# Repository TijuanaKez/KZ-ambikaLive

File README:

Ambika Live! (we'll call it that for now)

This project is a series of modifications (improvements) over the top of the YAM fork of the original firmware for Ambika.

Changes:

ENV/LFO/MOD slot cycling with page buttons:

	- Repeatedly pressing buttons for ENV/LFO and MOD pages now cycles through slots.
	- Makes for muscle memory access to what you’re after quickly. e.g (double click for LFO2)
	- Good for 2 handed operation.

Turbo patch name editing!

	- Can now press A,a or 1 to jump to those characters, insert space, or move cursor with buttons.
	- Super quick 2 handed name editing!
	- ( A | a | 1 | _ | <- | -> save | exit)

'Drum' modulation destinations.

	- Same as Osc1 and Osc2 destinations, but with +/-32 semitones range for wider pitch envelopes.
	- The standard coarse pitch mod destinations don't have enough range for good drum sounds, and the envelopes curves arent steep enough.
	- But, the standard envelopes can be 'squared' by using the modifiers for a steeper curve. Routing one of these 'squared' envelopes to 'drum' destination with an amount of 32, Ambika can achieve much better drum sounds or 808 like sounds.
	- e.g Modul.  1|srce mod1|dest drm1|amnt   32
	-     Modif.  1|in1  env1|in2  env1|oper prod  (squaring the Env1 envelope)

Solo polyphony mode:

	-Same as mono but only uses a single voice. Great if you designed a patch for a single voice (legato/glide) but want to load it onto a part that has multiple voices assigned and don’t want the unison/stacked sound.

Arp Latch Mode:

	-Acts like the arp latch on Microkorg. Pressing a key once triggers note on, a second time for note off.

Chord Sequencer mode:

	-In Chord Seq mode, the sequencer will pass each block of 4 consecutive notes on to the arp as a chord.
	-The 'lenp' parameter defines how many steps between chord changes.
	-The note sequence length is locked to 16 steps (4 chords) for now.
	-Use rests to reduce the number of notes in each chord.

Sequencer Tweaks:

	-Rests are now displayed similar to a tracker where '---' is displayed when there is no note assigned.
	-Makes for more visual drum sequences.

Performance Page Tweaks

	-When in the main performance page, the first 4 buttons now act as part mutes. Cool for jamming with the chord sequencer!
	-Button 5 resyncs the clocks. This is a bit of a workaround for the moment until I can get them to stay locked without having to resync (any ideas?)

Optional CC Maps (pref page 2)

	-Can choose between Ambika standard, Shruthi XT, and Novation Launchkey CC assignments (more to come).
	-Ideally these would be loadable from SDcard, but the only way I can think to fit them would be to use the boot loader to overwrite CC maps in progmem which is beyond my skills :frowning:

Unfortunately these mods will not be fully compatible with saved patches, though updating them would not be hard. It would mainly be checking the polyphony mode is correct, and resaving.

Work in progress…

Launchkey integration!

USB host for Launchkey via Arduino micro+micro USB Host via port 7 for connecting Launchkey directly to the Ambika.
Buss power the Arduino micro+Launchkey (might need regulator upgrade on ambika???)
Launchkey Sequencer mode: RGB pads will show sequence ‘playhead’ with one color, and knobs will edit either note, seq1 or seq2 depending on mode. Idle pads will show other colors whose intensity will represent the current sequencer values.
(‘Launchkey Seq’ mode is already in prefs page 2, but only shows the playhead now)

Source Code: Macros for enabling/disabling various functions to free up space temporarily to mess around.

The YAM fork of the original firmware can be found here (https://github.com/bjoeri/ambika).
As this is forked on top of YAM, all the YAM changes also apply.

Notes on building the source:

	- For the voicecard build to succeed, avr-gcc 4.3.3 must be used. Any later versions will build, but result in a silent voice card.
	- For the controller, avr-gcc 4.3.3 build will break our file size limit (61440 bytes)
	- But 4.5.1 will successfully build the controller and save us about 2700 bytes!!!

--- YAM Notes ---

Y A M - Yet Another Mutation

This is a project for an alternative firmware for Ambika, a hybrid MIDI polysynth and voicecard host from Mutable Instruments. 

Here's a short summary of changes _compared_ to official Ambika firmware:

* PolyBlep implementations replace the original band-limited 'saw' and 'square' oscillators for higher fidelity and less memory footprint (Polyblep implementation inspired by, but less general than, Emilies prototype for STM). 

* 'square' is now a Polyblep oscillator with more proper sounding PWM, i.e. more edginess, and no loudness drop for PWM modulation parameter above 0. 

* 'saw' is now a Polyblep oscillator (without any high pass pre-filtering and the modulation is different). The parameter for saw now add mix of a 2nd saw edge, resulting in a saw with sub oscillator (actually super oscillator) sound. 

* 'triangle' is no longer band-limited (to reduce memory footprint) and is folded (instead of clipped) upon modulation. 

* Added a quad PWM oscillator ('qpwm') very similar to the quad saw ('pad'). The modulation parameter simultaneously affects both detuning of the four pwm oscillators and the pulse width.

* Added an alternative FM oscillator ('fmfb') with feedback modulation. Just as for the regular FM oscillator, the modulation parameter defines the FM amount, but for modulation values above 64 increasing amount of feedback is added. At moderate levels the feedback adds 'grit'. At higher settings it adds digital distortion (deliberately left in).

* Added a 'csaw' Polyblep oscillator rather similar to the CS-80 inspired saw oscillator for Braids. Without modulation it's a plain saw (identical to 'saw'). Modulation adds a 'notch' discontinuity before the ramp.

* Ported phase57 mods for velocity and keyboard tracking to filter page and CC & NRPN assignments (104 and 105 respectively). Also, the active editing parameter is displayed in all uppercase characters. (http://blog.phase57.com/index.php/ambika/code for more details.) 

NOTES ON PATCH (PROGRAM) COMPATIBILITY with official Ambika firmware: 
Due to qualitative differences of the 'saw' and 'square' oscillators etc, levels may have to be adjusted somewhat to mimic original patches. If you really miss the original saw oscillator from the official firmware, this one is still available as 'oldsaw' (it's high-pass sampled and have a different character). In order to maximize patch (actually program) backwards compatibility, the added oscillators are put at the end of the oscillator selection (even though this means fmfb is not next to fm etc).

This repository was originally a copy of the Mutable Instruments GitHub Ambika repository at https://github.com/pichenettes/ambika
 
Original developer: Emilie Gillet (olivier@mutable-instruments.net)

The firmware is released under a GPL3.0 license. It includes a variant of the formant synthesis algorithm used in Peter Knight's Cantarino speech synthesizer.

The PCB layouts and schematics, documentation, analyses, simulations and 3D models are released under a Creative Commons cc-by-sa 3.0 license.

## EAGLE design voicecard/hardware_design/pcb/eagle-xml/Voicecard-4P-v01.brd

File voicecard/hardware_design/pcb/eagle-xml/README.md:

# Eagle XML resaves of the original voicecard designs

These are the original Mutable Instruments Ambika voicecard files (Eagle 5 binary,
in the parent directory) resaved as Eagle 9.7.0 XML. They come from
https://github.com/rhinocerose/synth-mutable-ambika (voicecard/hardware_design/pcb/*/eagle-xml/).

Provenance check, 2026-09-15: the binary originals in that repository are
byte-identical (MD5) to the ones in this tree, and the XML pair for the 4P is a
straight resave: 131 parts / 66 nets in the schematic, 92 elements / 66 signals on
the board. No design changes.

These XML files are what KiCad's Eagle importer needs (it cannot read the Eagle 5
binaries). Voicecard-4P-v01 is the source for the SMD/KiCad rebuild.

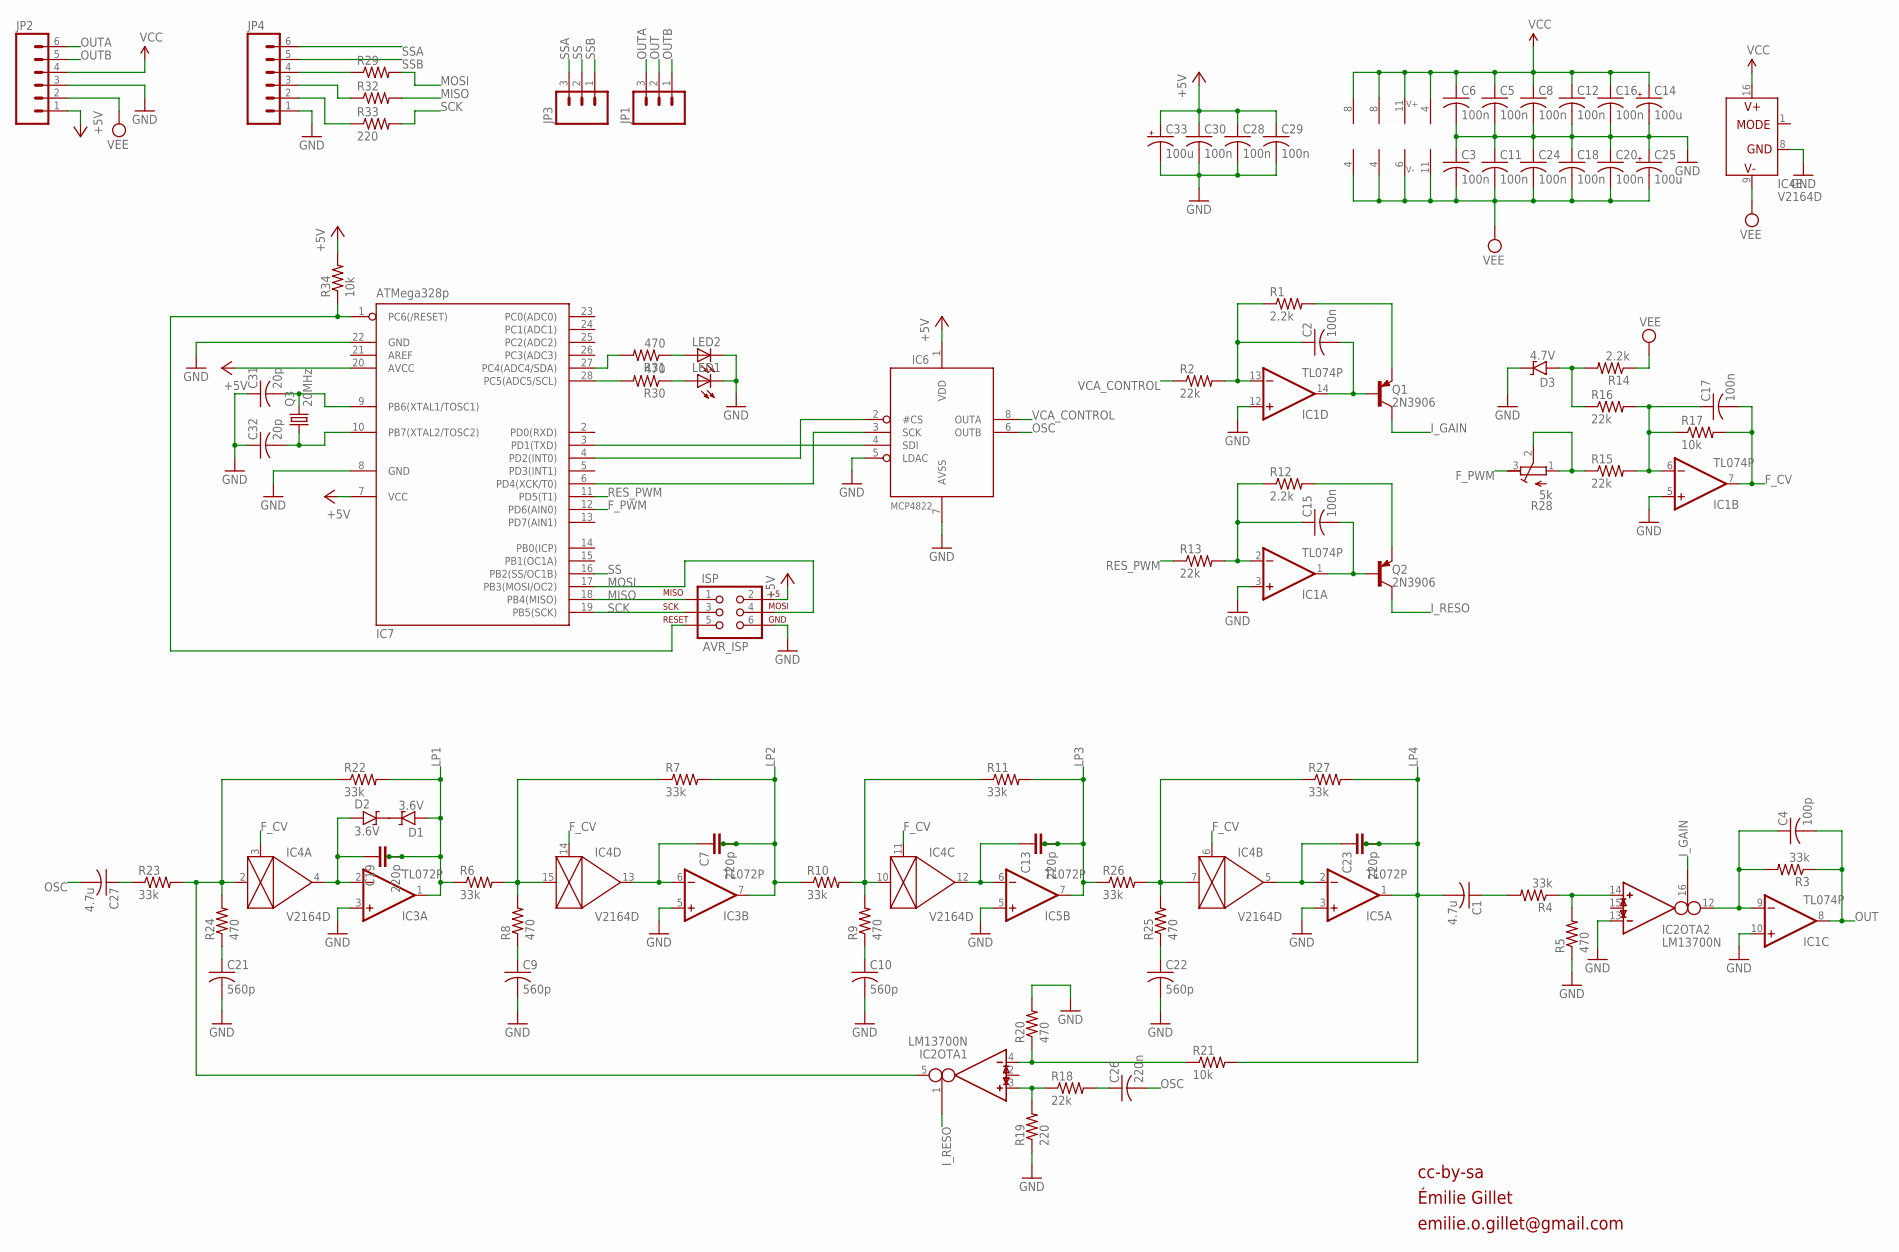
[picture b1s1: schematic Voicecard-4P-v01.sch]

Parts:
C1, C27: 4.7u; ENP11-6.3
C2, C3, C5, C6, C8, C11, C12, C15, C16, C17, C18, C20, C24, C28, C29, C30: 100n; C025-025X050
C4: 100p; C025-025X050
C7, C13, C19, C23: 220p; C2.5/5-4
C9, C10, C21, C22: 560p; C025-025X050
C14, C25, C33: 100u; E2,5-6
C26: 220n; C025-025X050
C31, C32: 20p; C025-025X050
D1, D2: 3.6V; D-5
D3: 4.7V; D-5
IC1: TL074P; DIL14
IC2: LM13700N; DIL16
IC3, IC5: TL072P; DIL08
IC4: V2164D; DIL16
IC6: MCP4822; DIL08
IC7: ATMega328p; DIL28-3
ISP: AVR_ISP; 2X3
JP1, JP3: M03PTH; 1X03
JP2, JP4: M06SIP; 1X06
LED1, LED2: LED3MM
Q1, Q2: 2N3906; TO92-
Q3: 20MHz; HC49U-V
R1, R12, R14: 2.2k; 0204/7
R2, R13, R15, R16, R18: 22k; 0204/7
R3, R4, R6, R7, R10, R11, R22, R23, R26, R27: 33k; 0204/7
R5, R8, R9, R20, R24, R25, R30, R31: 470; 0204/7
R17, R21, R34: 10k; 0204/7
R19, R29, R32, R33: 220; 0204/7
R28: 5k; RTRIM3296P

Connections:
+5V: C28.1, C29.1, C30.1, C33.+, IC6.1 (VDD), IC7.7 (VCC), IC7.20 (AVCC), ISP.2, JP2.1, R34.2
CAP_IN: C19.1, D2.A, IC3.2 (-IN), IC4.4 (OUT)
F_CV: C17.2, IC1.7 (OUT), IC4.3 (CTRL), IC4.6 (CTRL), IC4.11 (CTRL), IC4.14 (CTRL), R17.2
F_PWM: IC7.12 (PD6(AIN0)), R28.3 (A)
GND: C3.1, C5.2, C6.2, C8.2, C9.2, C10.2, C11.1, C12.2, C14.-, C16.2, C18.1, C20.1, C21.2, C22.2, C24.1, C25.+, C28.2, C29.2, C30.2, C31.1, C32.1, C33.-, D3.C, IC1.3 (+IN), IC1.5 (+IN), IC1.10 (+IN), IC1.12 (+IN), IC2.13 (IN_N), IC3.3 (+IN), IC3.5 (+IN), IC4.8 (GND), IC5.3 (+IN), IC5.5 (+IN), IC6.5 (LDAC), IC6.7 (AVSS), IC7.8 (GND), IC7.22 (GND), ISP.6, JP2.3, JP4.1, LED1.K (C), LED2.K (C), R5.1, R19.1, R20.2
I_GAIN: IC2.16 (I_BIAS), Q1.1 (C)
I_RESO: IC2.1 (I_BIAS), Q2.1 (C)
LEDS0: IC7.28 (PC5(ADC5/SCL)), R30.2
LP1: C19.2, C19.3, D1.A, IC3.1 (OUT), R6.1, R22.2
LP2: C7.2, C7.3, IC3.7 (OUT), R7.2, R10.1
LP3: C13.2, C13.3, IC5.7 (OUT), R11.2, R26.1
LP4: C1.- (2), C23.2, C23.3, IC5.1 (OUT), R21.2, R27.2
MISO: IC7.18 (PB4(MISO)), ISP.1, R32.2
MOSI: IC7.17 (PB3(MOSI/OC2)), ISP.4, R29.2
unnamed: C27.+ (1), R23.1
unnamed: C1.+ (1), R4.2
unnamed: IC6.4 (SDI), IC7.3 (PD1(TXD))
unnamed: C21.1, R24.1
unnamed: LED1.A, R30.1
unnamed: JP4.2, R33.1
unnamed: D3.A, R14.2, R16.1
unnamed: LED2.A, R31.1
unnamed: IC7.27 (PC4(ADC4/SDA)), R31.2
unnamed: C7.1, IC3.6 (-IN), IC4.13 (OUT)
unnamed: JP4.3, R32.1
unnamed: IC7.1 (PC6(/RESET)), ISP.5, R34.1
unnamed: IC6.3 (SCK), IC7.6 (PD4(XCK/T0))
unnamed: IC6.2 (#CS), IC7.4 (PD2(INT0))
unnamed: C13.1, IC4.12 (OUT), IC5.6 (-IN)
unnamed: JP4.4, R29.1
unnamed: IC4.10 (IN), R9.2, R10.2, R11.1
unnamed: C10.1, R9.1
unnamed: C22.1, R25.1
unnamed: IC4.7 (IN), R25.2, R26.2, R27.1
unnamed: C23.1, IC4.5 (OUT), IC5.2 (-IN)
unnamed: C9.1, R8.1
unnamed: C2.2, IC1.14 (OUT), Q1.2 (B)
unnamed: C15.2, IC1.1 (OUT), Q2.2 (B)
unnamed: IC2.4 (IN_N), R20.1, R21.1
unnamed: IC2.5 (OUT), IC4.2 (IN), R22.1, R23.2, R24.2
unnamed: IC2.3 (IN_P), R18.1, R19.2
unnamed: C26.1, R18.2
unnamed: IC2.14 (IN_P), R4.1, R5.2
unnamed: C17.1, IC1.6 (-IN), R15.2, R16.2, R17.1
unnamed: R15.1, R28.1 (E), R28.2 (S)
unnamed: D1.C, D2.C
unnamed: IC4.15 (IN), R6.2, R7.1, R8.2
unnamed: C15.1, IC1.2 (-IN), R12.1, R13.2
unnamed: C2.1, IC1.13 (-IN), R1.1, R2.2
unnamed: Q1.3 (E), R1.2
unnamed: Q2.3 (E), R12.2
unnamed: C4.1, IC1.9 (-IN), IC2.12 (OUT), R3.2
unnamed: C32.2, IC7.10 (PB7(XTAL2/TOSC2)), Q3.1
unnamed: C31.2, IC7.9 (PB6(XTAL1/TOSC1)), Q3.2
OSC: C26.2, C27.- (2), IC6.6 (OUTB)
OUT: C4.2, IC1.8 (OUT), JP1.2, R3.1
OUTA: JP1.3, JP2.6
OUTB: JP1.1, JP2.5
RES_PWM: IC7.11 (PD5(T1)), R13.1
SCK: IC7.19 (PB5(SCK)), ISP.3, R33.2
SS: IC7.16 (PB2(SS/OC1B)), JP3.2
SSA: JP3.3, JP4.6
SSB: JP3.1, JP4.5
VCA_CONTROL: IC6.8 (OUTA), R2.1
VCC: C5.1, C6.1, C8.1, C12.1, C14.+, C16.1, IC1.4 (V+), IC2.11 (V+), IC3.8 (V+), IC4.16 (V+), IC5.8 (V+), JP2.4
VEE: C3.2, C11.2, C18.2, C20.2, C24.2, C25.-, IC1.11 (V-), IC2.6 (V-), IC3.4 (V-), IC4.9 (V-), IC5.4 (V-), JP2.2, R14.1

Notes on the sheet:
cc-by-sa
Émilie Gillet
emilie.o.gillet@gmail.com

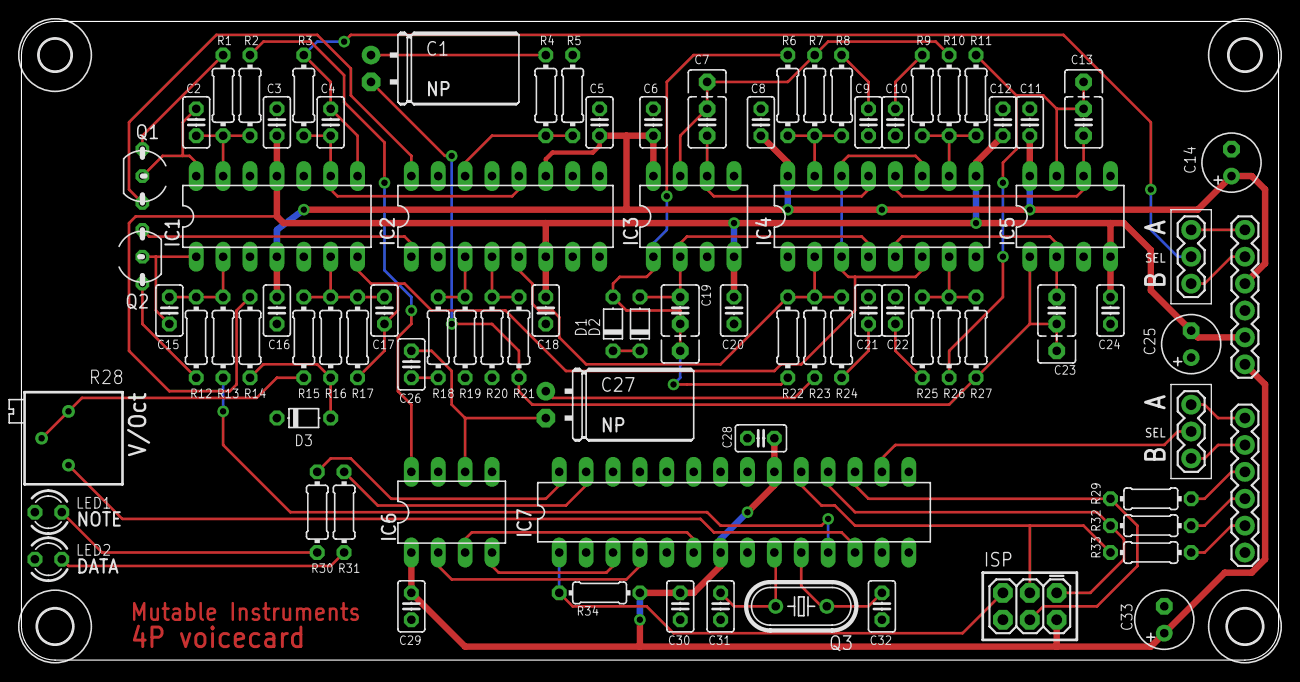
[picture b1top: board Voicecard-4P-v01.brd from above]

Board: 2 copper layers, 118.7 x 60.3 mm, 92 parts (0 on the bottom side), 66 nets.

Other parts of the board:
U$1, U$2: 3,0
U$4, U$5: 3,3
U$6: V2_LOGO_SMALL

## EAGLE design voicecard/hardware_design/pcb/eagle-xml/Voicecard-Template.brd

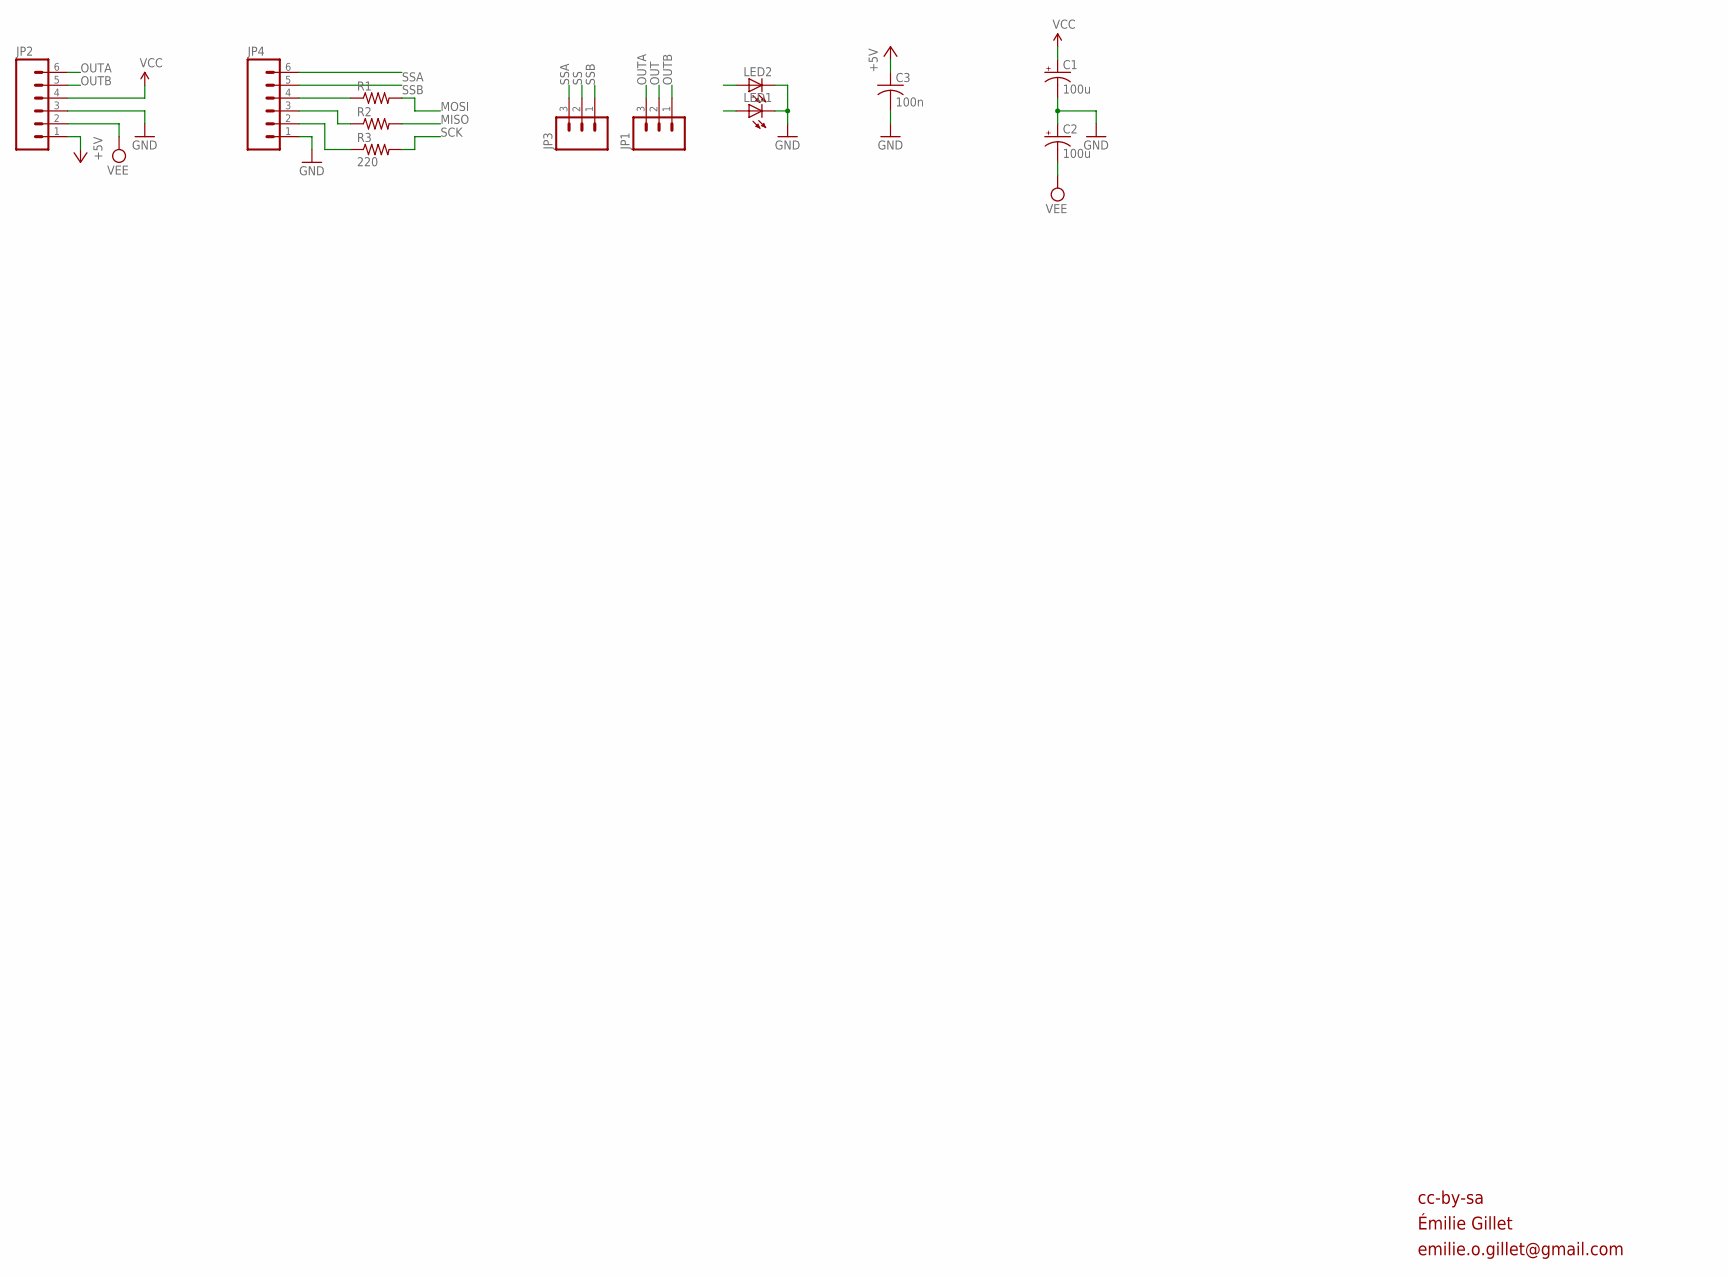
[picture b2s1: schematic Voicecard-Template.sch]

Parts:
C1, C2: 100u; E2,5-6
C3: 100n; C025-025X050
JP1, JP3: M03PTH; 1X03
JP2, JP4: M06SIP; 1X06
LED1, LED2: LED3MM
R1, R2, R3: 220; 0204/7

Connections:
+5V: C3.1, JP2.1
GND: C1.-, C2.+, C3.2, JP2.3, JP4.1, LED1.K (C), LED2.K (C)
MISO: R2.2
MOSI: R1.2
unnamed: JP4.2, R3.1
unnamed: JP4.3, R2.1
unnamed: JP4.4, R1.1
OUT: JP1.2
OUTA: JP1.3, JP2.6
OUTB: JP1.1, JP2.5
SCK: R3.2
SS: JP3.2
SSA: JP3.3, JP4.6
SSB: JP3.1, JP4.5
VCC: C1.+, JP2.4
VEE: C2.-, JP2.2

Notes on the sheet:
cc-by-sa
Émilie Gillet
emilie.o.gillet@gmail.com

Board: 2 copper layers, 16 parts (0 on the bottom side), 11 nets, no tracks yet.

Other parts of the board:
U$1, U$2: 3,0
U$3, U$4: 3,3

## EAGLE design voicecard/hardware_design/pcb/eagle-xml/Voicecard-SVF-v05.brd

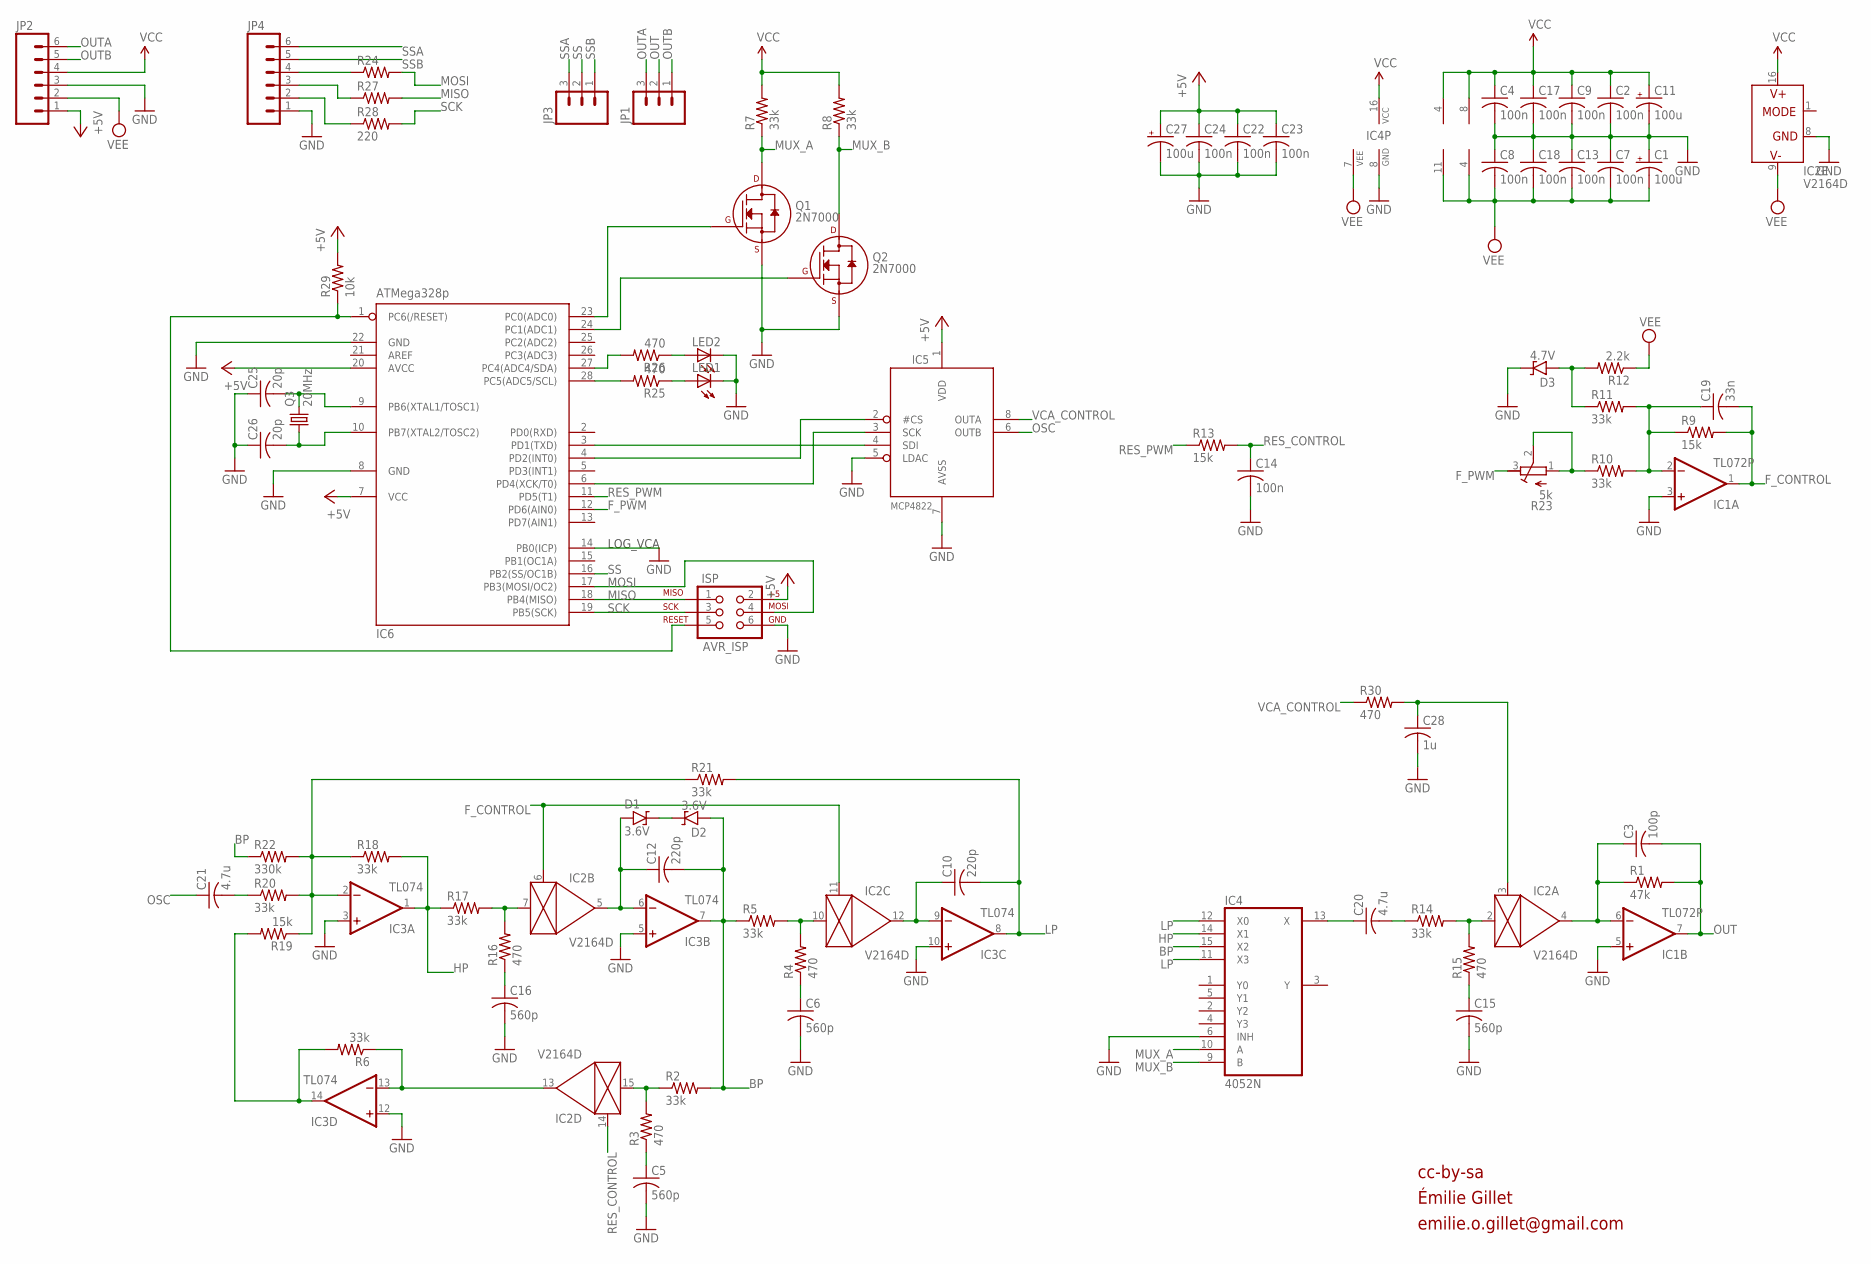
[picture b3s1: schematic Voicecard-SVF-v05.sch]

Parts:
C1, C11, C27: 100u; E2,5-6
C2, C4, C7, C8, C9, C13, C14, C17, C18, C22, C23: 100n; C025-025X050
C3: 100p; C025-025X050
C5, C6, C15, C16: 560p; C025-025X050
C10, C12: 220p; C025-025X050
C19: 33n; C050-025X075
C20, C21: 4.7u; ENP11-6.3
C24: 100n; C025-024X044
C25, C26: 20p; C025-024X044
C28: 1u; C050-025X075
D1, D2: 3.6V; D-5
D3: 4.7V; D-5
IC1: TL072P; DIL08
IC2: V2164D; DIL16
IC3: TL074; DIL14
IC4: 4052N; DIL16
IC5: MCP4822; DIL08
IC6: ATMega328p; DIL28-3
ISP: AVR_ISP; 2X3
JP1, JP3: M03PTH; 1X03
JP2, JP4: M06SIP; 1X06
LED1, LED2: LED3MM
Q1, Q2: 2N7000; TO-92
Q3: 20MHz; HC49U-V
R1: 47k; 0204/7
R2, R5, R6, R7, R8, R10, R11, R14, R17, R18, R20, R21: 33k; 0204/7
R3, R4, R15, R16, R25, R26, R30: 470; 0204/7
R9, R13, R19: 15k; 0204/7
R12: 2.2k; 0204/7
R22: 330k; 0204/7
R23: 5k; RTRIM3296P
R24, R27, R28: 220; 0204/7
R29: 10k; 0204/7

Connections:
+5V: C22.1, C23.1, C24.1, C27.+, IC5.1 (VDD), IC6.7 (VCC), IC6.20 (AVCC), ISP.2, JP2.1, R29.2
BP: C12.2, D2.A, IC3.7 (OUT), IC4.15 (X2), R2.2, R5.1, R22.1
FILTER_MIX1: C20.+ (1), IC4.13 (X)
F_CONTROL: C19.2, IC1.1 (OUT), IC2.6 (CTRL), IC2.11 (CTRL), R9.2
F_PWM: IC6.12 (PD6(AIN0)), R23.3 (A)
GND: C1.+, C2.2, C4.2, C5.2, C6.2, C7.1, C8.1, C9.2, C11.-, C13.1, C14.2, C15.2, C16.2, C17.2, C18.1, C22.2, C23.2, C24.2, C25.1, C26.1, C27.-, C28.2, D3.C, IC1.3 (+IN), IC1.5 (+IN), IC2.8 (GND), IC3.3 (+IN), IC3.5 (+IN), IC3.10 (+IN), IC3.12 (+IN), IC4.6 (INH), IC4.8 (GND), IC5.5 (LDAC), IC5.7 (AVSS), IC6.8 (GND), IC6.14 (PB0(ICP)), IC6.22 (GND), ISP.6, JP2.3, JP4.1, LED1.K (C), LED2.K (C), Q1.1 (S), Q2.1 (S)
HP: IC3.1 (OUT), IC4.14 (X1), R17.1, R18.2
LEDS0: IC6.28 (PC5(ADC5/SCL)), R25.2
LP: C10.2, IC3.8 (OUT), IC4.11 (X3), IC4.12 (X0), R21.2
MISO: IC6.18 (PB4(MISO)), ISP.1, R27.2
MOSI: IC6.17 (PB3(MOSI/OC2)), ISP.4, R24.2
MUX_A: IC4.10 (A), Q1.3 (D), R7.1
MUX_B: IC4.9 (B), Q2.3 (D), R8.1
unnamed: C21.- (2), R20.1
unnamed: IC5.4 (SDI), IC6.3 (PD1(TXD))
unnamed: IC6.23 (PC0(ADC0)), Q1.2 (G)
unnamed: C20.- (2), R14.1
unnamed: IC6.24 (PC1(ADC1)), Q2.2 (G)
unnamed: LED1.A, R25.1
unnamed: JP4.2, R28.1
unnamed: D3.A, R11.1, R12.2
unnamed: LED2.A, R26.1
unnamed: IC6.27 (PC4(ADC4/SDA)), R26.2
unnamed: IC3.2 (-IN), R18.1, R19.1, R20.2, R21.1, R22.2
unnamed: JP4.3, R27.1
unnamed: IC6.1 (PC6(/RESET)), ISP.5, R29.1
unnamed: IC5.3 (SCK), IC6.6 (PD4(XCK/T0))
unnamed: IC5.2 (#CS), IC6.4 (PD2(INT0))
unnamed: C6.1, R4.1
unnamed: JP4.4, R24.1
unnamed: C12.1, D1.A, IC2.5 (OUT), IC3.6 (-IN)
unnamed: IC2.15 (IN), R2.1, R3.2
unnamed: IC2.10 (IN), R4.2, R5.2
unnamed: C5.1, R3.1
unnamed: C10.1, IC2.12 (OUT), IC3.9 (-IN)
unnamed: IC2.7 (IN), R16.2, R17.2
unnamed: C16.1, R16.1
unnamed: IC2.13 (OUT), IC3.13 (-IN), R6.1
unnamed: C19.1, IC1.2 (-IN), R9.1, R10.2, R11.2
unnamed: R10.1, R23.1 (E), R23.2 (S)
unnamed: IC3.14 (OUT), R6.2, R19.2
unnamed: D1.C, D2.C
unnamed: C15.1, R15.1
unnamed: IC2.2 (IN), R14.2, R15.2
unnamed: C3.1, IC1.6 (-IN), IC2.4 (OUT), R1.1
unnamed: C26.2, IC6.10 (PB7(XTAL2/TOSC2)), Q3.1
unnamed: C25.2, IC6.9 (PB6(XTAL1/TOSC1)), Q3.2
NET55: C28.1, IC2.3 (CTRL), R30.2
OSC: C21.+ (1), IC5.6 (OUTB)
OUT: C3.2, IC1.7 (OUT), JP1.2, R1.2
OUTA: JP1.3, JP2.6
OUTB: JP1.1, JP2.5
RES_CONTROL: C14.1, IC2.14 (CTRL), R13.2
RES_PWM: IC6.11 (PD5(T1)), R13.1
SCK: IC6.19 (PB5(SCK)), ISP.3, R28.2
SS: IC6.16 (PB2(SS/OC1B)), JP3.2
SSA: JP3.3, JP4.6
SSB: JP3.1, JP4.5
VCA_CONTROL: IC5.8 (OUTA), R30.1
VCC: C2.1, C4.1, C9.1, C11.+, C17.1, IC1.8 (V+), IC2.16 (V+), IC3.4 (V+), IC4.16 (VCC), JP2.4, R7.2, R8.2
VEE: C1.-, C7.2, C8.2, C13.2, C18.2, IC1.4 (V-), IC2.9 (V-), IC3.11 (V-), IC4.7 (VEE), JP2.2, R12.1

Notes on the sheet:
cc-by-sa
Émilie Gillet
emilie.o.gillet@gmail.com
LOG_VCA

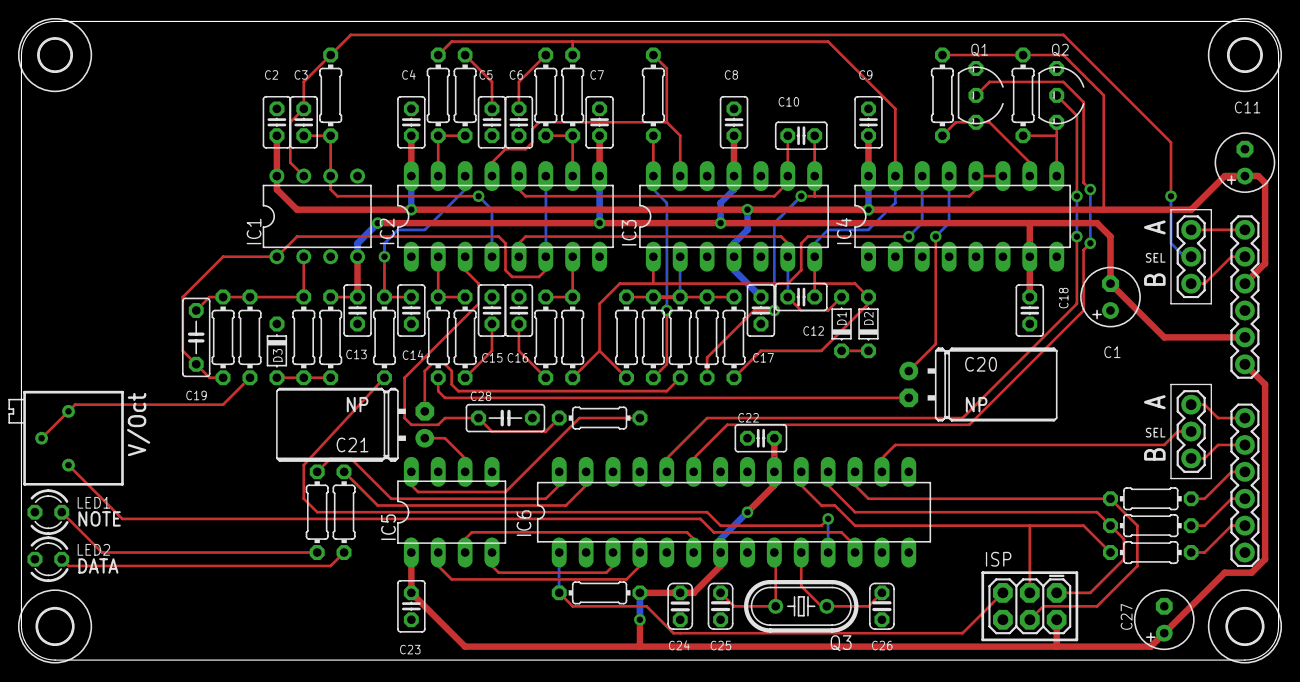
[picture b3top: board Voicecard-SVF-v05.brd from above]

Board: 2 copper layers, 118.7 x 60.3 mm, 83 parts (0 on the bottom side), 61 nets.

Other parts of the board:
U$1, U$2: 3,0
U$3: LAPINO_LARGE
U$4: SARASWATI
U$5, U$6: 3,3

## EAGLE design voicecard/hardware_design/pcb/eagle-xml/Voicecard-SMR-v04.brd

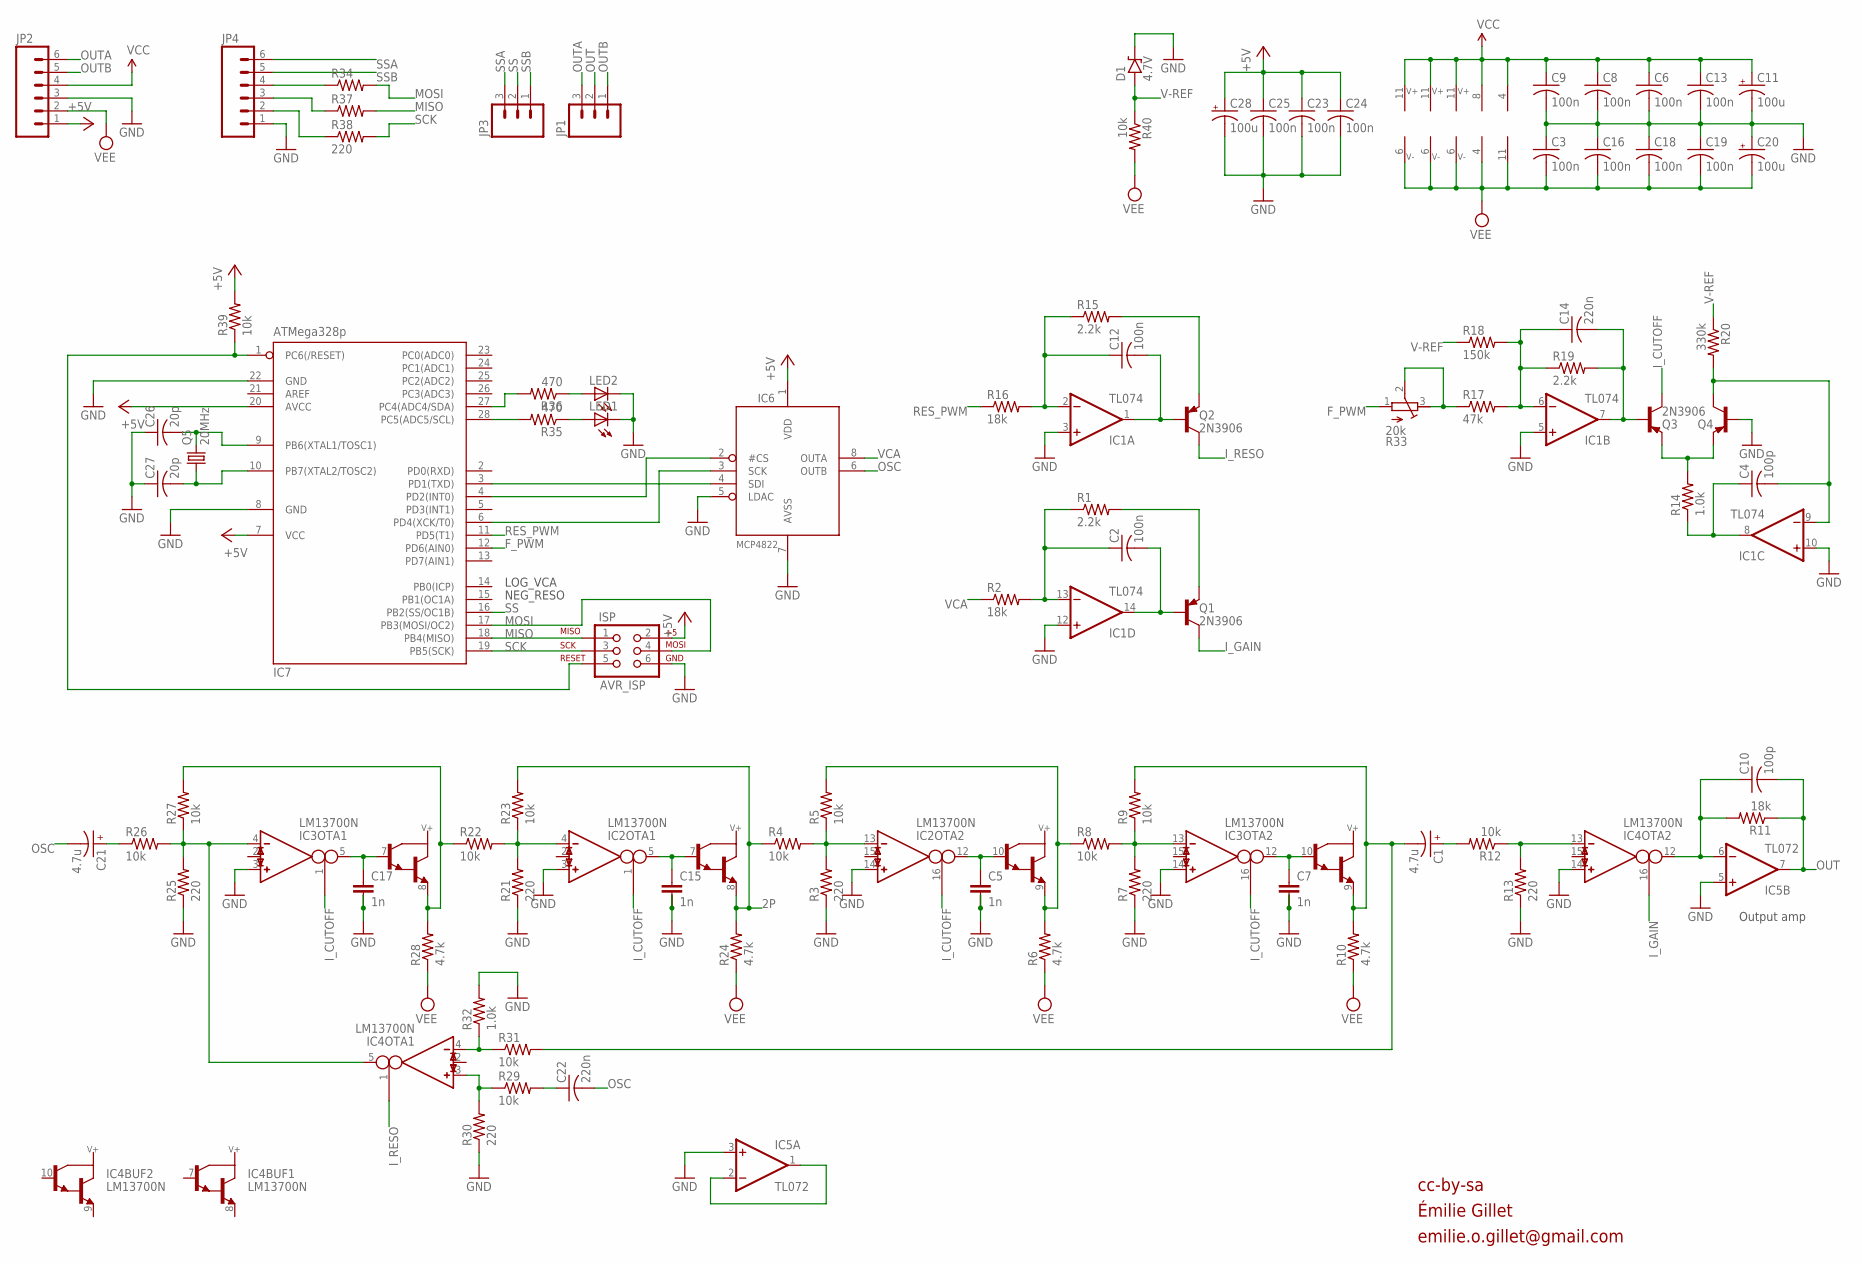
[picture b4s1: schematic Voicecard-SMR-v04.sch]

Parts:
C1, C21: 4.7u; E11-6.3
C2, C3, C6, C8, C9, C12, C13, C16, C18, C19, C23, C24: 100n; C025-025X050
C4, C10: 100p; C025-025X050
C5, C7, C15, C17: 1n; C2.5/5-2
C11, C20, C28: 100u; E2,5-6
C14, C22: 220n; C025-025X050
C25: 100n; C025-024X044
C26, C27: 20p; C025-024X044
D1: 4.7V; D-5
IC1: TL074; DIL14
IC2, IC3, IC4: LM13700N; DIL16
IC5: TL072; DIL08
IC6: MCP4822; DIL08
IC7: ATMega328p; DIL28-3
ISP: AVR_ISP; 2X3
JP1, JP3: M03PTH; 1X03
JP2, JP4: M06SIP; 1X06
LED1, LED2: LED3MM
Q1, Q2, Q3, Q4: 2N3906; TO92-
Q5: 20MHz; HC49U-V
R1, R15, R19: 2.2k; 0204/7
R2, R11, R16: 18k; 0204/7
R3, R7, R13, R21, R25, R30, R34, R37, R38: 220; 0204/7
R4, R5, R8, R9, R12, R22, R23, R26, R27, R29, R31, R39, R40: 10k; 0204/7
R6, R10, R24, R28: 4.7k; 0204/7
R14, R32: 1.0k; 0204/7
R17: 47k; 0204/7
R18: 150k; 0204/7
R20: 330k; 0204/7
R33: 20k; RTRIM3296P
R35, R36: 470; 0204/7

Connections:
2P: IC2.8 (E), R4.1, R23.2, R24.2
4P: C1.- (2), IC3.9 (E), R9.2, R10.2, R31.2
+5V: C23.1, C24.1, C25.1, C28.+, IC6.1 (VDD), IC7.7 (VCC), IC7.20 (AVCC), ISP.2, JP2.1, R39.2
F_PWM: IC7.12 (PD6(AIN0)), R33.1 (E)
GND: C3.1, C5.2, C5.3, C6.2, C7.2, C7.3, C8.2, C9.2, C11.-, C13.2, C15.2, C15.3, C16.1, C17.2, C17.3, C18.1, C19.1, C20.+, C23.2, C24.2, C25.2, C26.1, C27.1, C28.-, D1.C, IC1.3 (+IN), IC1.5 (+IN), IC1.10 (+IN), IC1.12 (+IN), IC2.3 (IN_P), IC2.14 (IN_P), IC3.3 (IN_P), IC3.14 (IN_P), IC4.14 (IN_P), IC5.3 (+IN), IC5.5 (+IN), IC6.5 (LDAC), IC6.7 (AVSS), IC7.8 (GND), IC7.22 (GND), ISP.6, JP2.3, JP4.1, LED1.K (C), LED2.K (C), Q4.2 (B), R3.1, R7.1, R13.1, R21.1, R25.1, R30.1, R32.2
I_CUTOFF: IC2.1 (I_BIAS), IC2.16 (I_BIAS), IC3.1 (I_BIAS), IC3.16 (I_BIAS), Q3.1 (C)
I_GAIN: IC4.16 (I_BIAS), Q1.1 (C)
I_RESO: IC4.1 (I_BIAS), Q2.1 (C)
MISO: IC7.18 (PB4(MISO)), ISP.1, R37.2
MOSI: IC7.17 (PB3(MOSI/OC2)), ISP.4, R34.2
unnamed: Q3.3 (E), Q4.3 (E), R14.2
unnamed: C14.2, IC1.7 (OUT), Q3.2 (B), R19.2
unnamed: IC6.4 (SDI), IC7.3 (PD1(TXD))
unnamed: C4.2, IC1.9 (-IN), Q4.1 (C), R20.2
unnamed: C21.+ (1), R26.1
unnamed: IC3.8 (E), R22.1, R27.2, R28.2
unnamed: LED1.A, R35.1
unnamed: JP4.2, R38.1
unnamed: C4.1, IC1.8 (OUT), R14.1
unnamed: LED2.A, R36.1
unnamed: IC7.27 (PC4(ADC4/SDA)), R36.2
unnamed: IC3.4 (IN_N), IC4.5 (OUT), R25.2, R26.2, R27.1
unnamed: JP4.3, R37.1
unnamed: IC7.1 (PC6(/RESET)), ISP.5, R39.1
unnamed: IC6.3 (SCK), IC7.6 (PD4(XCK/T0))
unnamed: IC6.2 (#CS), IC7.4 (PD2(INT0))
unnamed: IC2.4 (IN_N), R21.2, R22.2, R23.1
unnamed: JP4.4, R34.1
unnamed: C15.1, IC2.5 (OUT), IC2.7 (B)
unnamed: IC7.28 (PC5(ADC5/SCL)), R35.2
unnamed: IC2.13 (IN_N), R3.2, R4.2, R5.1
unnamed: IC5.1 (OUT), IC5.2 (-IN)
unnamed: C5.1, IC2.10 (B), IC2.12 (OUT)
unnamed: IC3.13 (IN_N), R7.2, R8.2, R9.1
unnamed: IC2.9 (E), R5.2, R6.2, R8.1
unnamed: C1.+ (1), R12.2
unnamed: C7.1, IC3.10 (B), IC3.12 (OUT)
unnamed: IC4.4 (IN_N), R31.1, R32.1
unnamed: C12.2, IC1.1 (OUT), Q2.2 (B)
unnamed: C2.2, IC1.14 (OUT), Q1.2 (B)
unnamed: C22.1, R29.2
unnamed: IC4.3 (IN_P), R29.1, R30.2
unnamed: IC4.13 (IN_N), R12.1, R13.2
unnamed: C14.1, IC1.6 (-IN), R17.2, R18.2, R19.1
unnamed: R17.1, R33.2 (S), R33.3 (A)
unnamed: C2.1, IC1.13 (-IN), R1.1, R2.2
unnamed: C12.1, IC1.2 (-IN), R15.1, R16.2
unnamed: Q2.3 (E), R15.2
unnamed: C17.1, IC3.5 (OUT), IC3.7 (B)
unnamed: Q1.3 (E), R1.2
unnamed: C10.1, IC4.12 (OUT), IC5.6 (-IN), R11.2
unnamed: C27.2, IC7.10 (PB7(XTAL2/TOSC2)), Q5.1
unnamed: C26.2, IC7.9 (PB6(XTAL1/TOSC1)), Q5.2
OSC: C21.- (2), C22.2, IC6.6 (OUTB)
OUT: C10.2, IC5.7 (OUT), JP1.2, R11.1
OUTA: JP1.3, JP2.6
OUTB: JP1.1, JP2.5
RES_PWM: IC7.11 (PD5(T1)), R16.1
SCK: IC7.19 (PB5(SCK)), ISP.3, R38.2
SS: IC7.16 (PB2(SS/OC1B)), JP3.2
SSA: JP3.3, JP4.6
SSB: JP3.1, JP4.5
V-REF: D1.A, R18.1, R20.1, R40.1
VCA: IC6.8 (OUTA), R2.1
VCC: C6.1, C8.1, C9.1, C11.+, C13.1, IC1.4 (V+), IC2.11 (V+), IC3.11 (V+), IC4.11 (V+), IC5.8 (V+), JP2.4
VEE: C3.2, C16.2, C18.2, C19.2, C20.-, IC1.11 (V-), IC2.6 (V-), IC3.6 (V-), IC4.6 (V-), IC5.4 (V-), JP2.2, R6.1, R10.1, R24.1, R28.1, R40.2

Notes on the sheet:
cc-by-sa
LOG_VCA
NEG_RESO
Output amp
Émilie Gillet
emilie.o.gillet@gmail.com

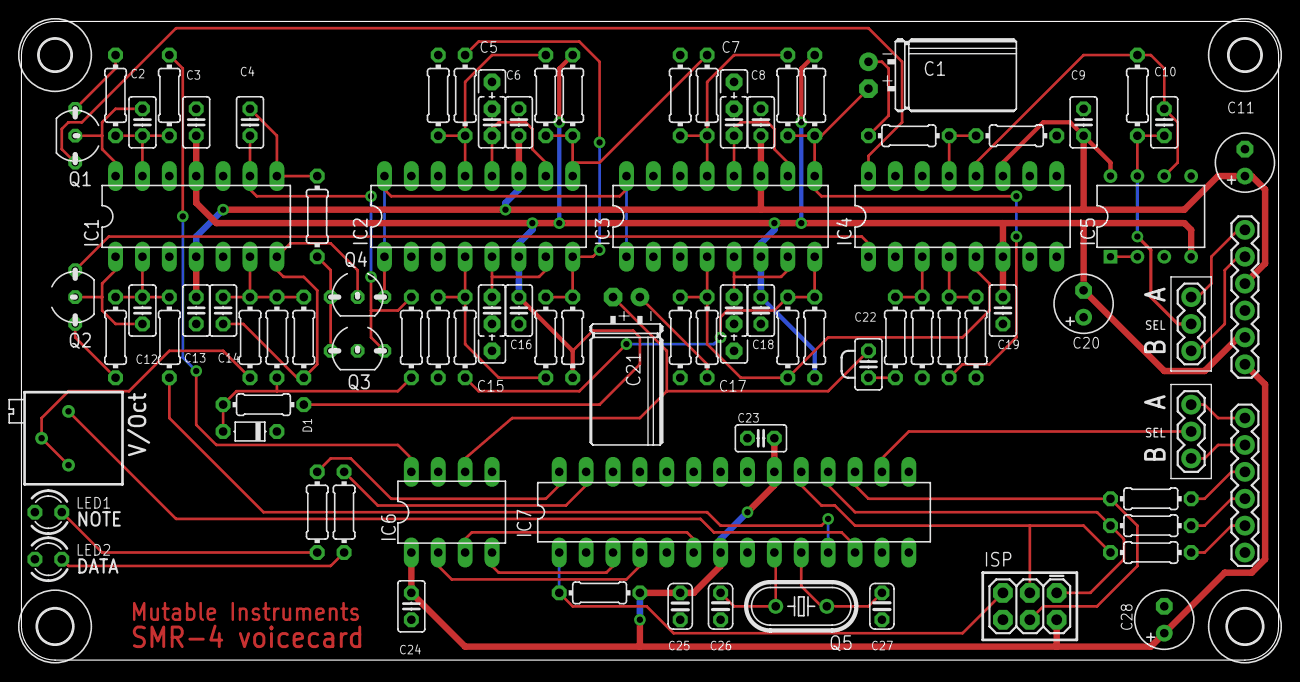
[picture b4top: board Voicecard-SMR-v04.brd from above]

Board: 2 copper layers, 118.7 x 60.3 mm, 93 parts (0 on the bottom side), 66 nets.

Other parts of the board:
U$1, U$2: 3,0
U$4, U$5: 3,3
U$6: V2_LOGO_SMALL
